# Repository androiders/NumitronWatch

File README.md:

# NumitronWatch
A clock based on atmega8 and numitron IV-9 as displays

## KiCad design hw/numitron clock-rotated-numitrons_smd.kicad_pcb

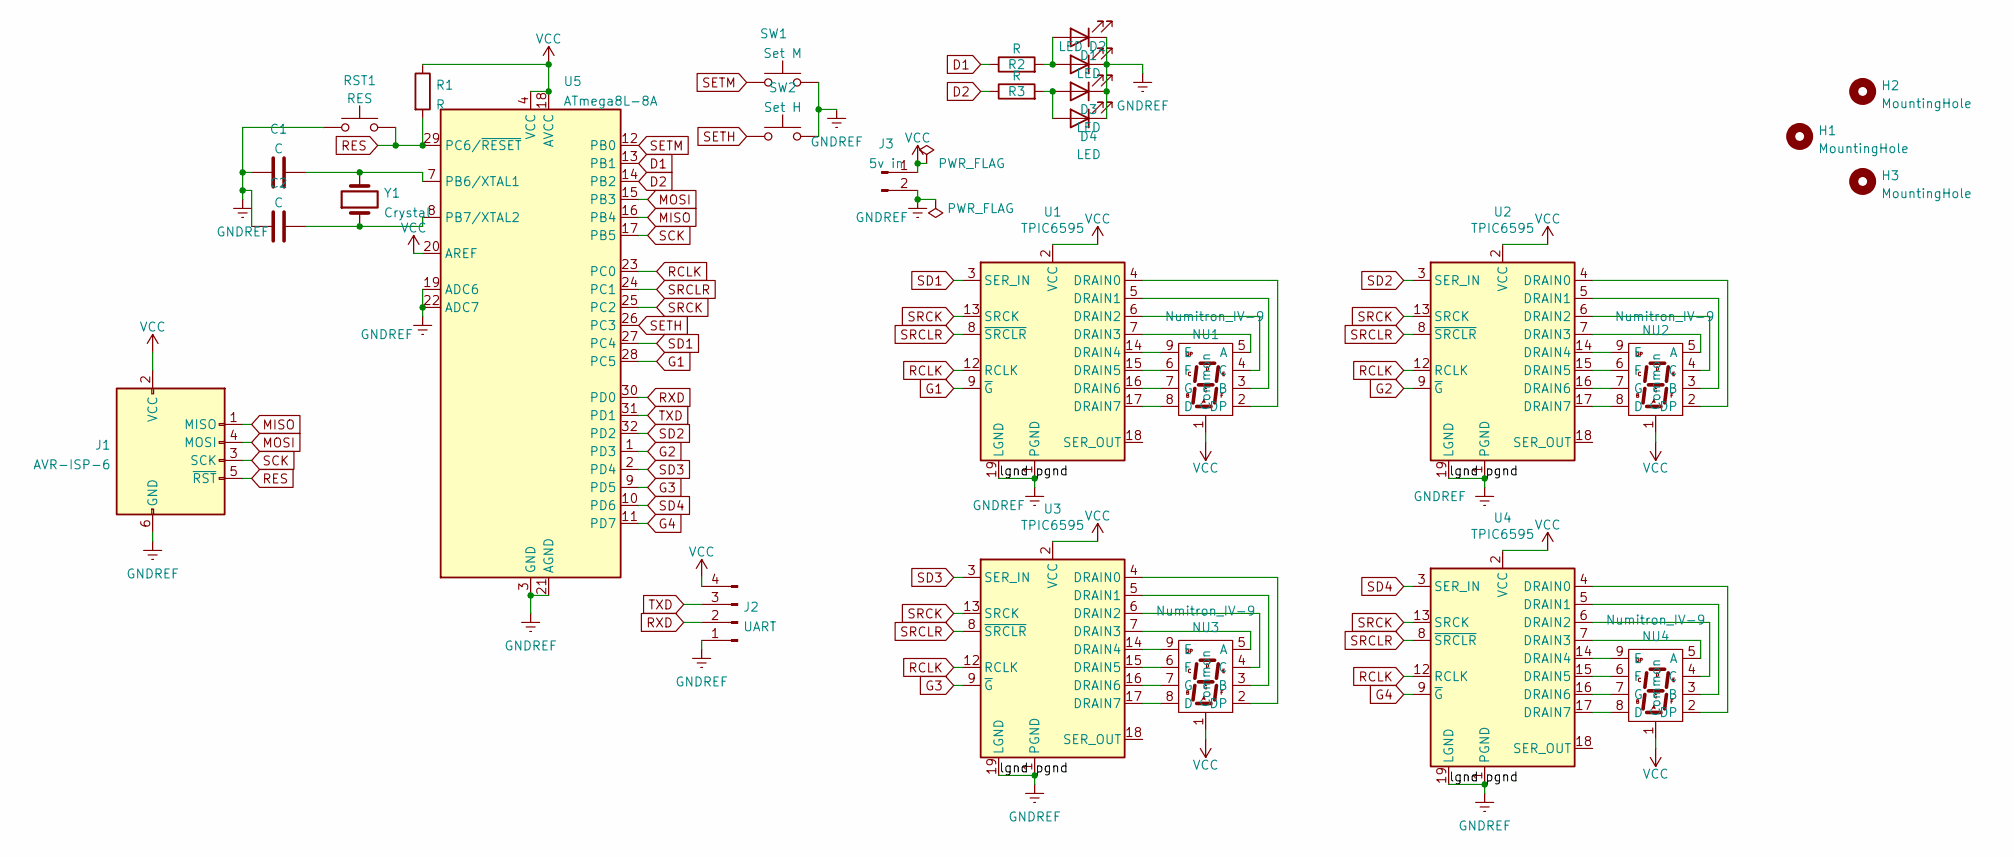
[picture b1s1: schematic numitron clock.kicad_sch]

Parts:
C1, C2: C; C_Disc_D3.8mm_W2.6mm_P2.50mm
D1, D4: LED; LED_1206_3216Metric
D2, D3: LED; LED_D5.0mm
H1, H2, H3: MountingHole; MountingHole_3.2mm_M3
J1: AVR-ISP-6; IDC-Header_2x03_P2.54mm_Vertical
J2: UART; PinHeader_1x04_P2.54mm_Vertical
J3: 5v in; TerminalBlock_Phoenix_MKDS-1,5-2-5.08_1x02_P5.08mm_Horizont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
NU1, NU2, NU3, NU4: Numitron_IV-9; numitron iv-9
R1, R2, R3: R; R_0805_2012Metric_Pad1.20x1.40mm_HandSolder
RST1: RES; SW_SPST_CK_RS282G05A3
SW1: Set M; SW_SPST_CK_RS282G05A3
SW2: Set H; SW_SPST_CK_RS282G05A3
U1, U2, U3, U4: TPIC6595; SOIC-20W_7.5x12.8mm_P1.27mm
U5: ATmega8L-8A; TQFP-32_7x7mm_P0.8mm
Y1: Crystal; Crystal_Round_D1.5mm_Vertical

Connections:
D1: R2.1, U5.13 (PB1)
D2: R3.1, U5.14 (PB2)
G1: U1.9 (~G), U5.28 (PC5)
G2: U2.9 (~G), U5.1 (PD3)
G3: U3.9 (~G), U5.9 (PD5)
G4: U4.9 (~G), U5.11 (PD7)
GNDREF: C1.1, C2.1, D1.1 (K), D2.1 (K), D3.1 (K), D4.1 (K), J1.6 (GND), J2.1, J3.2, RST1.1, SW1.2, SW2.2, U1.1 (PGND), U1.10 (PGND), U1.11 (PGND), U1.19 (LGND), U1.20 (PGND), U2.1 (PGND), U2.10 (PGND), U2.11 (PGND), U2.19 (LGND), U2.20 (PGND), U3.1 (PGND), U3.10 (PGND), U3.11 (PGND), U3.19 (LGND), U3.20 (PGND), U4.1 (PGND), U4.10 (PGND), U4.11 (PGND), U4.19 (LGND), U4.20 (PGND), U5.3 (GND), U5.5 (GND), U5.19 (ADC6), U5.21 (AGND), U5.22 (ADC7)
MISO: J1.1 (MISO), U5.16 (PB4)
MOSI: J1.4 (MOSI), U5.15 (PB3)
unnamed: C1.2, U5.7 (PB6/XTAL1), Y1.2
unnamed: C2.2, U5.8 (PB7/XTAL2), Y1.1
unnamed: D1.2 (A), D2.2 (A), R2.2
unnamed: D3.2 (A), D4.2 (A), R3.2
unnamed: NU1.2 (DP), U1.4 (DRAIN0)
unnamed: NU1.3 (B), U1.5 (DRAIN1)
unnamed: NU1.4 (C), U1.6 (DRAIN2)
unnamed: NU1.5 (A), U1.7 (DRAIN3)
unnamed: NU1.6 (F), U1.15 (DRAIN5)
unnamed: NU1.7 (G), U1.16 (DRAIN6)
unnamed: NU1.8 (D), U1.17 (DRAIN7)
unnamed: NU1.9 (E), U1.14 (DRAIN4)
unnamed: NU2.2 (DP), U2.4 (DRAIN0)
unnamed: NU2.3 (B), U2.5 (DRAIN1)
unnamed: NU2.4 (C), U2.6 (DRAIN2)
unnamed: NU2.5 (A), U2.7 (DRAIN3)
unnamed: NU2.6 (F), U2.15 (DRAIN5)
unnamed: NU2.7 (G), U2.16 (DRAIN6)
unnamed: NU2.8 (D), U2.17 (DRAIN7)
unnamed: NU2.9 (E), U2.14 (DRAIN4)
unnamed: NU3.2 (DP), U3.4 (DRAIN0)
unnamed: NU3.3 (B), U3.5 (DRAIN1)
unnamed: NU3.4 (C), U3.6 (DRAIN2)
unnamed: NU3.5 (A), U3.7 (DRAIN3)
unnamed: NU3.6 (F), U3.15 (DRAIN5)
unnamed: NU3.7 (G), U3.16 (DRAIN6)
unnamed: NU3.8 (D), U3.17 (DRAIN7)
unnamed: NU3.9 (E), U3.14 (DRAIN4)
unnamed: NU4.2 (DP), U4.4 (DRAIN0)
unnamed: NU4.3 (B), U4.5 (DRAIN1)
unnamed: NU4.4 (C), U4.6 (DRAIN2)
unnamed: NU4.5 (A), U4.7 (DRAIN3)
unnamed: NU4.6 (F), U4.15 (DRAIN5)
unnamed: NU4.7 (G), U4.16 (DRAIN6)
unnamed: NU4.8 (D), U4.17 (DRAIN7)
unnamed: NU4.9 (E), U4.14 (DRAIN4)
RCLK: U1.12 (RCLK), U2.12 (RCLK), U3.12 (RCLK), U4.12 (RCLK), U5.23 (PC0)
RES: J1.5 (~RST), R1.2, RST1.2, U5.29 (PC6/~RESET)
RXD: J2.2, U5.30 (PD0)
SCK: J1.3 (SCK), U5.17 (PB5)
SD1: U1.3 (SER_IN), U5.27 (PC4)
SD2: U2.3 (SER_IN), U5.32 (PD2)
SD3: U3.3 (SER_IN), U5.2 (PD4)
SD4: U4.3 (SER_IN), U5.10 (PD6)
SETH: SW2.1, U5.26 (PC3)
SETM: SW1.1, U5.12 (PB0)
SRCK: U1.13 (SRCK), U2.13 (SRCK), U3.13 (SRCK), U4.13 (SRCK), U5.25 (PC2)
SRCLR: U1.8 (~SRCLR), U2.8 (~SRCLR), U3.8 (~SRCLR), U4.8 (~SRCLR), U5.24 (PC1)
TXD: J2.3, U5.31 (PD1)
VCC: J1.2 (VCC), J2.4, J3.1, NU1.1 (Common), NU2.1 (Common), NU3.1 (Common), NU4.1 (Common), R1.1, U1.2 (VCC), U2.2 (VCC), U3.2 (VCC), U4.2 (VCC), U5.4 (VCC), U5.6 (VCC), U5.18 (AVCC), U5.20 (AREF)

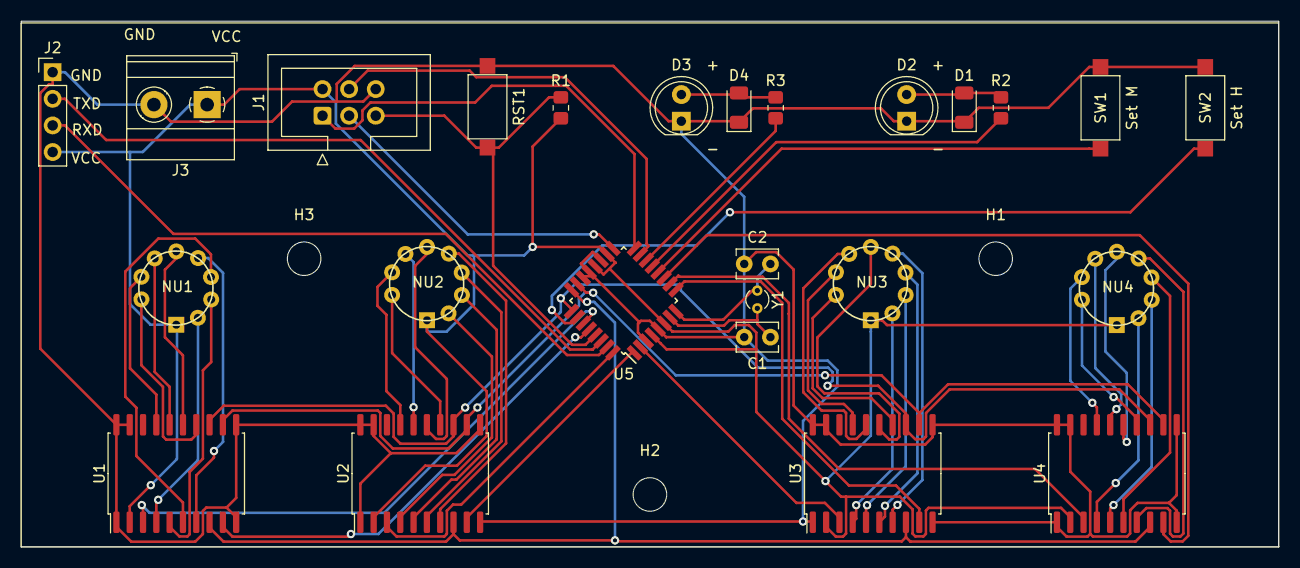
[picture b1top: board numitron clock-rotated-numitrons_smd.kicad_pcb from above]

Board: 2 copper layers, 120.0 x 50.2 mm, 28 parts (0 on the bottom side), 59 nets.

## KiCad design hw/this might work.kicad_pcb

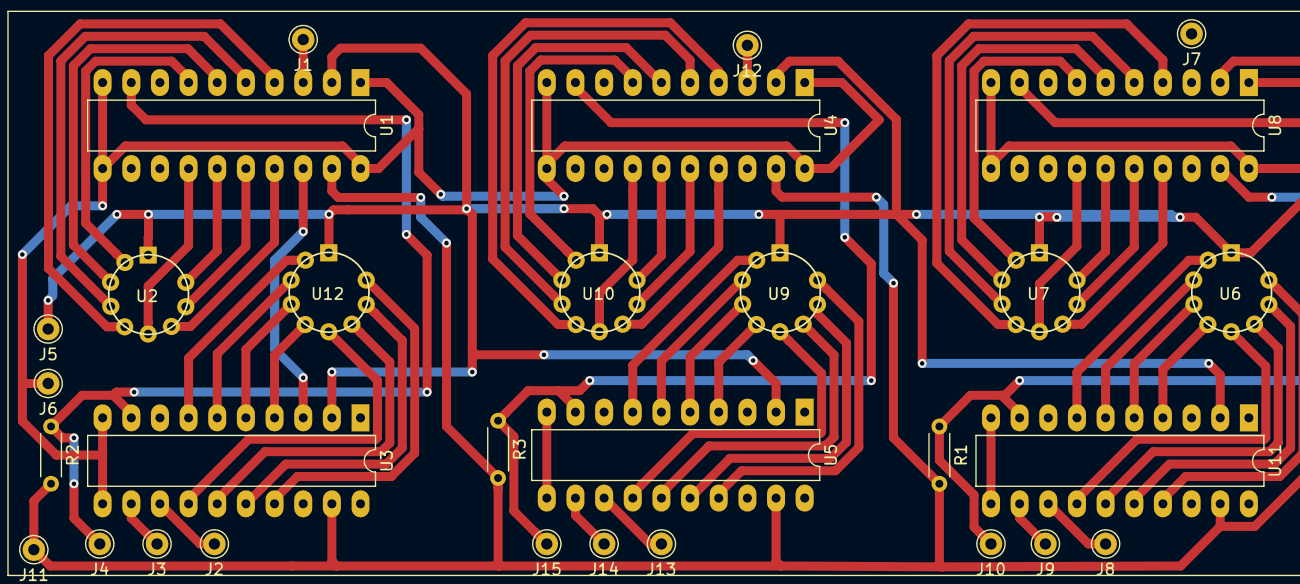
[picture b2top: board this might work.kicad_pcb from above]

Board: 2 copper layers, 30 parts (0 on the bottom side), 66 nets.

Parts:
J1: serial in; Pin_D1.0mm_L10.0mm
J2: serial clk; Pin_D1.0mm_L10.0mm
J3: rclk; Pin_D1.0mm_L10.0mm
J4: enable; Pin_D1.0mm_L10.0mm
J5: Vcc in; Pin_D1.0mm_L10.0mm
J6: Pwr gnd; Pin_D1.0mm_L10.0mm
J7: ser in 3; Pin_D1.0mm_L10.0mm
J8: srck 3; Pin_D1.0mm_L10.0mm
J9: rclk 3; Pin_D1.0mm_L10.0mm
J10: enable 3; Pin_D1.0mm_L10.0mm
J11: logic gnd; Pin_D1.0mm_L10.0mm
J12: ser in 2; Pin_D1.0mm_L10.0mm
J13: srck 2; Pin_D1.0mm_L10.0mm
J14: rclk 2; Pin_D1.0mm_L10.0mm
J15: enable 2; Pin_D1.0mm_L10.0mm
R1, R2, R3: R; R_Axial_DIN0204_L3.6mm_D1.6mm_P5.08mm_Horizontal
U1, U3, U4, U5, U8, U11: TPIC6595; DIP-20_W7.62mm_LongPads
U2, U6, U7, U9, U10, U12: Numitron_IV-9; numitron iv-9

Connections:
/lgnd: J11.1, R1.2, R2.2, R3.2, U1.19, U3.19, U4.19, U5.19, U8.19, U11.19
/pgnd: J6.1, U1.1, U1.10, U1.11, U1.20, U3.1, U3.10, U3.11, U3.20, U4.1, U4.10, U4.11, U4.20, U5.1, U5.10, U5.11, U5.20, U8.1, U8.10, U8.11, U8.20, U11.1, U11.10, U11.11, U11.20
unnamed: J1.1, U1.3
unnamed: J2.1, U1.13, U3.13
unnamed: J3.1, U1.12, U3.12
unnamed: J4.1, R2.1, U1.9, U3.9
unnamed: J5.1, U1.2, U2.1, U3.2, U4.2, U5.2, U6.1, U7.1, U8.2, U9.1, U10.1, U11.2, U12.1
unnamed: J7.1, U8.3
unnamed: J8.1, U8.13, U11.13
unnamed: J9.1, U8.12, U11.12
unnamed: J10.1, R1.1, U8.9, U11.9
unnamed: J12.1, U4.3
unnamed: J13.1, U4.13, U5.13
unnamed: J14.1, U4.12, U5.12
unnamed: J15.1, R3.1, U4.9, U5.9
unnamed: U1.4, U2.5
unnamed: U1.5, U2.4
unnamed: U1.6, U2.3
unnamed: U1.7, U2.2
unnamed: U1.14, U2.6
unnamed: U1.15, U2.9
unnamed: U1.16, U2.8
unnamed: U1.17, U2.7
unnamed: U1.18, U3.3
unnamed: U4.18, U5.3
unnamed: U5.4, U9.5
unnamed: U5.5, U9.4
unnamed: U5.6, U9.3
unnamed: U5.7, U9.2
unnamed: U5.14, U9.6
unnamed: U5.15, U9.7
unnamed: U5.16, U9.8
unnamed: U5.17, U9.9
unnamed: U7.2, U8.7
unnamed: U7.3, U8.6
unnamed: U7.4, U8.5
unnamed: U7.5, U8.4
unnamed: U7.6, U8.14
unnamed: U7.7, U8.17
unnamed: U7.8, U8.16
unnamed: U7.9, U8.15
unnamed: U4.7, U10.2
unnamed: U4.6, U10.3
unnamed: U4.5, U10.4
unnamed: U4.4, U10.5
unnamed: U4.14, U10.6
unnamed: U4.17, U10.7
unnamed: U4.16, U10.8
unnamed: U4.15, U10.9
unnamed: U8.18, U11.3
unnamed: U6.5, U11.4
unnamed: U6.4, U11.5
unnamed: U6.3, U11.6
unnamed: U6.2, U11.7
unnamed: U6.6, U11.14
unnamed: U6.7, U11.15
unnamed: U6.8, U11.16
unnamed: U6.9, U11.17
unnamed: U3.7, U12.2
unnamed: U3.6, U12.3
unnamed: U3.5, U12.4
unnamed: U3.4, U12.5
unnamed: U3.14, U12.6
unnamed: U3.15, U12.7
unnamed: U3.16, U12.8
unnamed: U3.17, U12.9

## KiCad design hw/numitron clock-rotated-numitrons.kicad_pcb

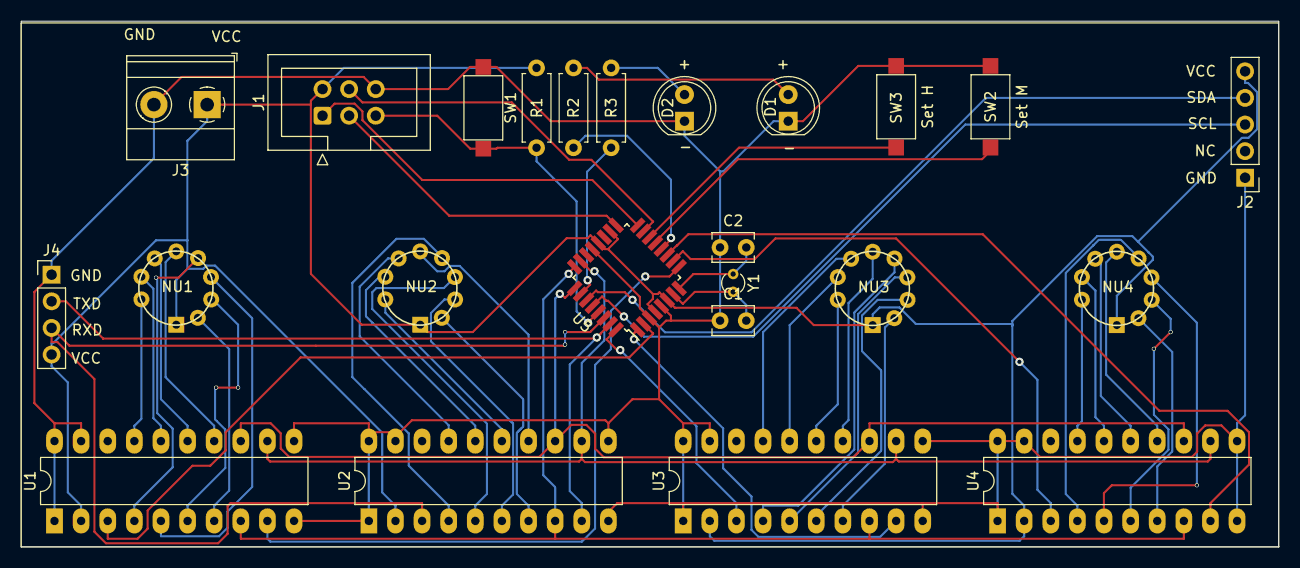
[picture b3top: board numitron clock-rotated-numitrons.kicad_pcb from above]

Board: 2 copper layers, 120.0 x 50.2 mm, 24 parts (0 on the bottom side), 59 nets.

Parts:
C1, C2: C; C_Disc_D3.8mm_W2.6mm_P2.50mm
D1, D2: LED; LED_D5.0mm
J1: AVR-ISP-6; IDC-Header_2x03_P2.54mm_Vertical
J2: rtc; PinHeader_1x05_P2.54mm_Vertical
J3: 5v in; TerminalBlock_Phoenix_MKDS-1,5-2-5.08_1x02_P5.08mm_Horizont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
J4: UART; PinHeader_1x04_P2.54mm_Vertical
NU1, NU2, NU3, NU4: Numitron_IV-9; numitron iv-9
R1, R2, R3: R; R_Axial_DIN0207_L6.3mm_D2.5mm_P7.62mm_Horizontal
SW1: RST; SW_SPST_CK_RS282G05A3
SW2: Set M; SW_SPST_CK_RS282G05A3
SW3: Set H; SW_SPST_CK_RS282G05A3
U1, U2, U3, U4: TPIC6595; DIP-20_W7.62mm_LongPads
U5: ATmega8L-8A; TQFP-32_7x7mm_P0.8mm
Y1: Crystal; Crystal_Round_D1.5mm_Vertical

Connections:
D1: R2.1, U5.12 (PB0)
D2: R3.1, U5.26 (PC3)
G1: J4.2, U2.9 (~G), U5.31 (PD1)
G2: U3.9 (~G), U5.1 (PD3)
G3: U1.9 (~G), U5.9 (PD5)
G4: U4.9 (~G), U5.11 (PD7)
GNDREF: C1.1, C2.1, D1.1 (K), D2.1 (K), J1.6 (GND), J2.1, J3.2, J4.1, SW1.1, SW2.2, SW3.2, U1.1 (PGND), U1.10 (PGND), U1.11 (PGND), U1.19 (LGND), U1.20 (PGND), U2.1 (PGND), U2.10 (PGND), U2.11 (PGND), U2.19 (LGND), U2.20 (PGND), U3.1 (PGND), U3.10 (PGND), U3.11 (PGND), U3.19 (LGND), U3.20 (PGND), U4.1 (PGND), U4.10 (PGND), U4.11 (PGND), U4.19 (LGND), U4.20 (PGND), U5.3 (GND), U5.5 (GND), U5.21 (AGND)
MISO: J1.1 (MISO), U5.16 (PB4)
MOSI: J1.4 (MOSI), U5.15 (PB3)
unnamed: C1.2, U5.7 (PB6/XTAL1), Y1.2
unnamed: C2.2, U5.8 (PB7/XTAL2), Y1.1
unnamed: D1.2 (A), R2.2
unnamed: D2.2 (A), R3.2
unnamed: J2.3, U5.28 (PC5)
unnamed: J2.4, U5.27 (PC4)
unnamed: NU1.2 (DP), U1.7 (DRAIN3)
unnamed: NU1.3 (B), U1.6 (DRAIN2)
unnamed: NU1.4 (C), U1.5 (DRAIN1)
unnamed: NU1.5 (A), U1.4 (DRAIN0)
unnamed: NU1.6 (F), U1.14 (DRAIN4)
unnamed: NU1.7 (G), U1.15 (DRAIN5)
unnamed: NU1.8 (D), U1.16 (DRAIN6)
unnamed: NU1.9 (E), U1.17 (DRAIN7)
unnamed: NU3.2 (DP), U3.7 (DRAIN3)
unnamed: NU3.3 (B), U3.6 (DRAIN2)
unnamed: NU3.4 (C), U3.5 (DRAIN1)
unnamed: NU3.5 (A), U3.4 (DRAIN0)
unnamed: NU3.6 (F), U3.14 (DRAIN4)
unnamed: NU3.7 (G), U3.17 (DRAIN7)
unnamed: NU3.8 (D), U3.16 (DRAIN6)
unnamed: NU3.9 (E), U3.15 (DRAIN5)
unnamed: SW2.1, U5.13 (PB1)
unnamed: SW3.1, U5.14 (PB2)
unnamed: NU2.5 (A), U2.4 (DRAIN0)
unnamed: NU2.4 (C), U2.5 (DRAIN1)
unnamed: NU2.3 (B), U2.6 (DRAIN2)
unnamed: NU2.2 (DP), U2.7 (DRAIN3)
unnamed: NU2.6 (F), U2.14 (DRAIN4)
unnamed: NU2.9 (E), U2.15 (DRAIN5)
unnamed: NU2.8 (D), U2.16 (DRAIN6)
unnamed: NU2.7 (G), U2.17 (DRAIN7)
unnamed: NU4.5 (A), U4.4 (DRAIN0)
unnamed: NU4.4 (C), U4.5 (DRAIN1)
unnamed: NU4.3 (B), U4.6 (DRAIN2)
unnamed: NU4.2 (DP), U4.7 (DRAIN3)
unnamed: NU4.6 (F), U4.14 (DRAIN4)
unnamed: NU4.7 (G), U4.15 (DRAIN5)
unnamed: NU4.8 (D), U4.16 (DRAIN6)
unnamed: NU4.9 (E), U4.17 (DRAIN7)
RCLK: U1.12 (RCLK), U2.12 (RCLK), U3.12 (RCLK), U4.12 (RCLK), U5.23 (PC0)
RST: J1.5 (~RST), R1.2, SW1.2, U5.29 (PC6/~RESET)
SCK: J1.3 (SCK), U5.17 (PB5)
SD1: J4.3, U2.3 (SER_IN), U5.30 (PD0)
SD2: U3.3 (SER_IN), U5.32 (PD2)
SD3: U1.3 (SER_IN), U5.2 (PD4)
SD4: U4.3 (SER_IN), U5.10 (PD6)
SRCK: U1.13 (SRCK), U2.13 (SRCK), U3.13 (SRCK), U4.13 (SRCK), U5.25 (PC2)
SRCLR: U1.8 (~SRCLR), U2.8 (~SRCLR), U3.8 (~SRCLR), U4.8 (~SRCLR), U5.24 (PC1)
VCC: J1.2 (VCC), J2.5, J3.1, J4.4, NU1.1 (Common), NU2.1 (Common), NU3.1 (Common), NU4.1 (Common), R1.1, U1.2 (VCC), U2.2 (VCC), U3.2 (VCC), U4.2 (VCC), U5.4 (VCC), U5.6 (VCC), U5.18 (AVCC), U5.20 (AREF)

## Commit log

2022-09-26 added hw files
2022-09-26 added sw files
2022-09-26 time control program
2022-09-28 updated time ctrl script
2022-09-28 version of pcb with more smd components
2022-10-06 fixed stupid bug
2022-10-09 updated to latest design
2022-11-17 final release?
2022-11-18 readded set mode and fixed nr 8
2022-11-18 small fix for shorter blink
